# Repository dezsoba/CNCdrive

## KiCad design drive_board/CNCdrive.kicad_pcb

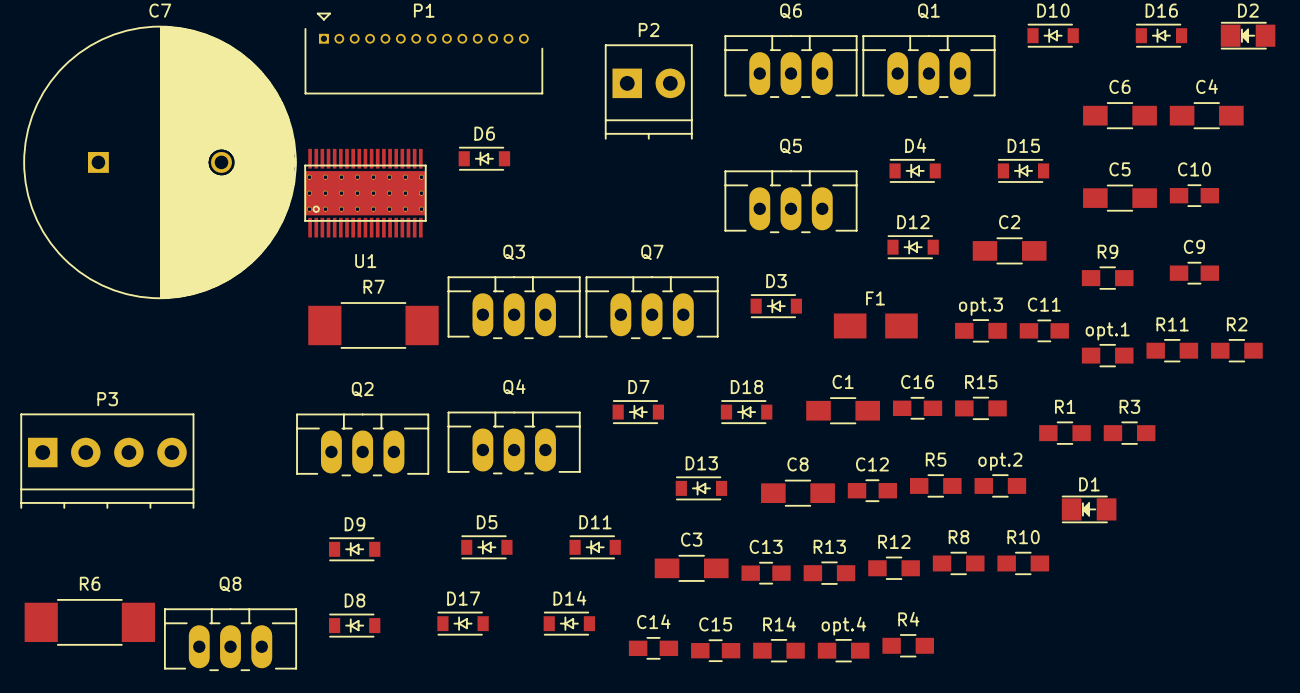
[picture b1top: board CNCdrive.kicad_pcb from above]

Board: 2 copper layers, 66 parts (0 on the bottom side), 50 nets, no tracks yet.

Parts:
C1: 100u; C_1206_HandSoldering
C2: 10n; C_1206_HandSoldering
C3, C6: 100n; C_1206_HandSoldering
C4, C5: 1u; C_1206_HandSoldering
C7: 1000u; C_Radial_D22_L41_P10
C8: 1n; C_1206_HandSoldering
C9, C10, C11, C12, C13, C14, C15, C16: snub; C_0805_HandSoldering
D1, D2: LED; LED_1206
D3, D4, D5, D6, D7, D8, D9, D10: ZENER opt.; SOD-123
D11, D12, D13, D14, D15, D16, D17, D18: D_Schottky; SOD-123
F1: 5A; Fuse_SMD1206_HandSoldering
P1: CONN_01X14; Connector_Molex_PicoBlade_53048-1410
P2: CONN_01X02; TerminalBlock_Pheonix_PT-3.5mm_2pol
P3: CONN_01X04; TerminalBlock_Pheonix_PT-3.5mm_4pol
Q1, Q2, Q3, Q4, Q5, Q6, Q7, Q8: Q_NMOS_GDS; TO-220_Neutral123_Vertical_LargePads
R1: 24K; R_0805_HandSoldering
R2: 1K6; R_0805_HandSoldering
R3, R4, R5: 3K3; R_0805_HandSoldering
R6, R7: R; R_2512_HandSoldering
R8, R9, R10, R11, R12, R13, R14, R15: snub; R_0805_HandSoldering
U1: DRV8711; drv8711
opt.1, opt.2, opt.3, opt.4: R; R_0805_HandSoldering

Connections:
+5V: C3.1, R2.1, R3.1, R4.1, R5.1, U1.6
+48V: C1.1, C2.1, C5.2, C7.1, D12.1, D14.1, D16.1, D17.1, F1.2, Q1.2, Q3.2, Q5.2, Q7.2, R1.1, R8.1, R10.1, R11.1, R13.1, U1.4
/AISENP: C10.2, C15.2, D4.2, D6.2, D11.2, D18.2, Q2.3, Q4.3, R6.2, U1.34
/BEMF: C8.1, P1.13, U1.20
/BIN1: P1.5, U1.12
/BIN2: P1.6, U1.13
/BISENP: C13.2, C16.2, D8.2, D10.2, D13.2, D15.2, Q6.3, Q8.3, R7.2, U1.25
/DIR/AIN2: P1.4, U1.11
/RESET: P1.2, U1.9
/SCLK: P1.7, U1.14
/SCS: P1.9, U1.16
/SDATI: P1.8, U1.15
/SDATO: P1.10, R5.2, U1.17
/STEP/AIN1: P1.3, U1.10
/~FAULT: P1.11, R4.2, U1.18
/~SLEEP: P1.1, U1.8
/~STALL/BEMFV: P1.12, R3.2, U1.19
GND: C7.2, P2.2, R6.1, R7.1
GNDD: C1.2, C2.2, C3.2, C4.2, C8.2, D1.1, D2.1, P1.14, U1.5, U1.29, U1.38
unnamed: C4.1, U1.7
unnamed: C5.1, U1.3
unnamed: C6.1, U1.1
unnamed: C6.2, U1.2
unnamed: C9.1, R8.2
unnamed: C9.2, D5.2, D11.1, D16.2, P3.2, Q3.3, Q4.2, R9.1, U1.30
unnamed: C10.1, R9.2
unnamed: C11.1, R10.2
unnamed: C11.2, D7.2, D12.2, D13.1, P3.3, Q5.3, Q6.2, R15.1, U1.28
unnamed: C12.1, R11.2
unnamed: C12.2, D9.2, D14.2, D15.1, P3.4, Q7.3, Q8.2, R12.1, U1.21
unnamed: C13.1, R12.2
unnamed: C14.1, R13.2
unnamed: C14.2, D3.2, D17.2, D18.1, P3.1, Q1.3, Q2.2, R14.1, U1.37
unnamed: C15.1, R14.2
unnamed: C16.1, R15.2
unnamed: D1.2, R1.2
unnamed: D2.2, R2.2
unnamed: D3.1, Q1.1, U1.36
unnamed: D4.1, Q2.1, opt.1.1
unnamed: D5.1, Q3.1, U1.31
unnamed: D6.1, Q4.1, opt.2.1
unnamed: D7.1, Q5.1, U1.27
unnamed: D8.1, Q6.1, opt.3.1
unnamed: D9.1, Q7.1, U1.22
unnamed: D10.1, Q8.1, opt.4.1
unnamed: F1.1, P2.1
unnamed: U1.23, opt.4.2
unnamed: U1.26, opt.3.2
unnamed: U1.32, opt.2.2
unnamed: U1.35, opt.1.2

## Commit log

2016-02-25 Second
2016-02-26 new folders for boards
2016-02-26 added footprints
2016-02-26 added stm32 footprint + schematics
2016-02-26 added most parts
2016-02-27 main parts added, most values are correct
2016-02-27 added reference design
2016-03-03 Almost finshed, fully commented
2016-03-03 new GND for digital
2016-03-03 drive board done
2016-03-06 added snubber, drive board is 100% done
2016-03-11 associated footprints, connectors, fuse, leds might need change
2016-03-11 added footprints, leds, fuse , conns may change
2016-03-11 added snubber design pdf
